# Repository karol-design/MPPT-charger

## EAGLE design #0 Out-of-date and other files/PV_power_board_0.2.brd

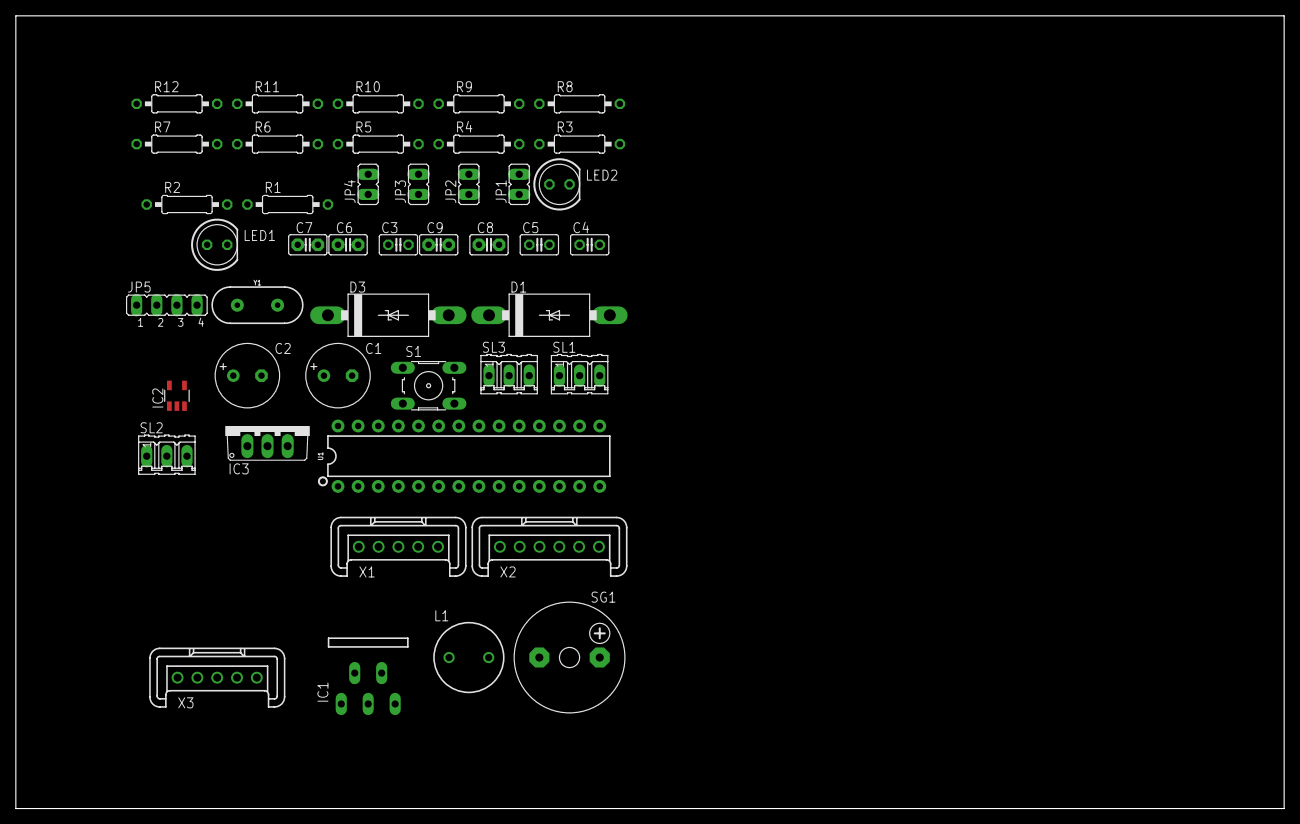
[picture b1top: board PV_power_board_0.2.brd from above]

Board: 2 copper layers, 160.0 x 100.0 mm, 44 parts (0 on the bottom side), 34 nets, no tracks yet.

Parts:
C1: 330µF; E3,5-8
C2: 100µF; E3,5-8
C3: 10µF; C025-025X050
C4: 0.33µF; C025-025X050
C5: 0.1µF; C025-025X050
C6, C7: 22p; C2.5-2
C8, C9: 100n; C2.5-2
D1: 1N5908; C4111-15
D3: STPS2L60; C4111-15
IC1: LM2576T; TO220-5
IC2: LMV358; SOT23-5
IC3: 7805TV; TO220V
JP1, JP2, JP3, JP4: JP1
JP5: JP4
L1: 330µH; 6000-XXXX-RC
LED1, LED2: LED5MM
R1, R12: 10k; 0207/10
R2: 33k; 0207/10
R3: 4.7k; 0207/10
R4, R6, R9: 1k; 0207/10
R5: 4.7; 0207/10
R7, R10: 120R; 0207/10
R8: 12k; 0207/10
R11: 220R; 0207/10
S1: B3F-10XX
SG1: F/CM12P
SL1: BATTERY; 03P
SL2: PV_PANEL; 03P
SL3: LOAD; 03P
U1: 328P; DIP28
X1: I_SENSOR; MKS1855-6-0-505
X2: BT_MODULE; MKS1856-6-0-606
X3: PROGRAM_PORT; MKS1855-6-0-505
Y1: 16MHz; HC49US

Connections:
+5V: C5.1, C9.2, IC2.5, IC3.3, JP4.2, JP5.4, LED1.A, R1.2, R12.1, U1.7, U1.20, X1.4, X3.5
BAT+: C1.+, C4.1, IC3.1, JP1.2, JP3.1, L1.1, R5.2, R8.1
BAT_VOLT: R5.1, R6.2, U1.25
DEV0: JP5.1, U1.27
DEV1: JP5.2, U1.26
FDBK: IC2.3, IC2.4, R9.1
GND: C1.-, C2.-, C3.2, C4.2, C5.2, C6.1, C7.1, C8.1, C9.1, D1.A, IC1.3, IC2.2, IC3.2, JP2.2, JP5.3, LED2.K, R4.1, R6.1, R7.2, S1.3, S1.4, SG1.-, SL1.2, SL1.3, SL3.2, SL3.3, U1.8, U1.22, X1.3, X2.4, X3.4
LM_ENABLE: IC1.5, R1.1
LM_FEEDBACK: IC1.4, R8.2, R9.2
LM_VIN: C2.+, IC1.1, R3.2, X1.2
unnamed: D1.C, IC1.2, L1.2
unnamed: C3.1, IC2.1, R2.1
unnamed: D3.C, X1.1
unnamed: LED1.K, R7.1
unnamed: D3.A, SL2.3
unnamed: JP1.1, SL3.1
unnamed: C6.2, U1.9, Y1.2
unnamed: R11.2, U1.14
unnamed: C7.2, U1.10, Y1.1
unnamed: JP3.2, SL1.1
unnamed: R10.2, U1.15
unnamed: LED2.A, R10.1
unnamed: C8.2, U1.21
unnamed: R11.1, SG1.+
unnamed: U1.6, X2.2
unnamed: U1.11, X2.3
unnamed: JP2.1, SL2.1, SL2.2
unnamed: JP4.1, X2.5
PV_CURRENT: U1.24, X1.5
PV_VOLT: R3.1, R4.2, U1.23
PWM: R2.2, U1.5
RESET: R12.2, S1.1, S1.2, U1.1, X3.1
RXD: U1.2, X3.3
TXD: U1.3, X3.2

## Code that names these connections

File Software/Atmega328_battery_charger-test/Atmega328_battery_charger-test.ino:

/*  Name: MPPT Solar Charger with Bluetooth communication | Battery charger test code
 *  Author: Karol Wojsław
 *  Date: 20/04/2021 (last release)
 *  Description: For test purposes only. This code is intended to be used for the test of 12V battery charger. For the test follow
 *  following procedure: Upload the code --> Connet the power supply --> Connect the battery --> Establish serial connection --> 
 *  --> Turn on the logger and validate first incoming data --> Leave the charger for >10 hours -->  Save and analyse the data
 *  
 *  Before the test change: timeMain, Vin_mV, Vout_float, Vout_bulk, V_ChargingDrop, PV_cur_Vofset
 */ 

#include <Wire.h>
#include <Adafruit_MCP4725.h>

/*Define pin allocations on Arduino board */
#define BAT_VOLT_PIN    A0
#define PV_VOLT_PIN     A1
#define PV_CURRENT_PIN  A2
#define LM_ENABLE_PIN   4

/*Fill in values below after callibration for improved precision of measurements and charger performance */
#define Vin_mV 5000 //Atmega328 supply voltage in mV - increased by - mV for more precise calculations (systematic error)
#define Vout_float 100 //Voltage that has to be set on FDBK pin to obtain float mode output voltage (13.70 V)
#define Vout_bulk 55 //Voltage that has to be set on FDBK pin to obtain float mode output voltage (14.65 V)
#define V_ChargingDrop 200 //Voltage to be subtracted when measureing the actual voltage on the battery
#define PV_cur_Vofset 320 //voltage in mV to be subtracted from PV_current sensor readings (systematic error)
#define R3  5150 
#define R4  980
#define R5  5070
#define R6  980

Adafruit_MCP4725 MCP4725_DAC; //Create MCP4725_DAC object

unsigned int n = 1; //Variable with current report issue

/*Define time intervals for different loops */
const unsigned long timeMain = 600000; //Time between main loop iterations (600000 ms = 600 seconds)


void setup(){
  //Input-output pin mode definition
  pinMode(BAT_VOLT_PIN, INPUT);
  pinMode(PV_VOLT_PIN, INPUT);
  pinMode(PV_CURRENT_PIN, INPUT);
  pinMode(LM_ENABLE_PIN, OUTPUT);

  //Output state change to default on startup
  digitalWrite(LM_ENABLE_PIN, HIGH); //Turn off LM2576 switching buck converter by default

  delay(10000); 

  Serial.begin(9600); //Standard serial port configuration (baud rate: 9600)
  Serial.print("Initialising charger code...\n");

  MCP4725_DAC.begin(0x60); //MCP4725 digital DAC I2C configuration (Adress: 0x60)
  SetCharging(Vout_float); //Set the charging voltage to Vout_float by default
  
  delay(5000);
}


void loop(){
  //Variables declaration
  unsigned long CHA_voltage, BAT_voltage, PV_voltage, PV_current, currentTime, tempTime, timeDifference = 0;
  bool Bulk = false;

  Serial.print("Main loop entered...\n\n"); //Header for logged data
  Serial.print("___________________________________________________________\n"); //Header for logged data
  Serial.print("No.\tMode\tCH_V\tBAT_V\tPV_V\tPV_I\tPower\tSOC\n"); //Header for logged data

  CHA_voltage = measureAverage(BAT_VOLT_PIN, 100, R5, R6); //Measure charging voltage
  /* Check state of charge of the battery before executing while loop and decide if Bulk or Float charging mode should be entered */
  digitalWrite(LM_ENABLE_PIN, HIGH); //Turn off LM2576 for measurements
  delay(1000); //Wait 1 second before the measurement
  BAT_voltage = measureAverage(BAT_VOLT_PIN, 100, R5, R6); //Measure battery voltage
  if(BAT_voltage < 13200){
    Bulk = true; //Set Bulk to 1 if the Battery voltage is lower than 13.2V
  }else{
    Bulk = false; //Set Bulk to 0 if the Battery voltage is higher than 13.2V
  }

  PV_voltage = measureAverage(PV_VOLT_PIN, 100, R3, R4);
  PV_current = (((measureAverage(PV_CURRENT_PIN, 100, 0, 1)-PV_cur_Vofset)*4)/6);
  generateReport(CHA_voltage, BAT_voltage, PV_voltage, PV_current, Bulk); //Send report over USB serial port

  /* Main loop of the code set to regularly check state of charge of the battery */
  while(true){
    currentTime = millis(); //Save current execution time
    tempTime = currentTime; //Set tempTime to currentTime at the beginning of the loop
    timeDifference = 0; //Set timeDifference to 0
    
    /* ------------------------------------------------------------ */
    /* ---------------- Enter bulk charging mode -------------------*/
    while(Bulk == true && timeDifference < timeMain){
      SetCharging(Vout_bulk); //Set the charging voltage to default Bulk voltage (14.65 V)
      digitalWrite(LM_ENABLE_PIN, LOW); //Turn on LM2576
      PV_current = (((measureAverage(PV_CURRENT_PIN, 100, 0, 1)*42)/60)-PV_cur_Vofset); //No voltage div, hence R1=0 & R2=1, 1 mA = 0.8 mV   
      if(PV_current < 300){
        Bulk = false;
      }
      
      delay(1000);

      currentTime = millis();
      timeDifference = currentTime - tempTime;  
    }

    /* ------------------------------------------------------------ */
    /* -------------- Enter float-storage charging mode ----------- */
    while(Bulk == false && timeDifference < timeMain){
      SetCharging(Vout_float); //Set the charging voltage to default float voltage (13.70 V)

      currentTime = millis();
      timeDifference = currentTime - tempTime; 
    }

    CHA_voltage = measureAverage(BAT_VOLT_PIN, 100, R5, R6); //Measure charging voltage
    PV_voltage = measureAverage(PV_VOLT_PIN, 100, R3, R4);
    PV_current = ((((measureAverage(PV_CURRENT_PIN, 100, 0, 1)-PV_cur_Vofset)*4)/6));
    
    /* Check state of charge of the battery and decide if Bulk or Float charging mode should be executed */
    digitalWrite(LM_ENABLE_PIN, HIGH); //Turn off LM2576 for measurements

    if(Bulk){
      delay(30000); //Wait 30 seconds before the measurement if the last mode was Bulk
    }else{
      delay(5000); //Wait 5 seconds before the measurement if the last mode was Float
    }
    
    BAT_voltage = measureAverage(BAT_VOLT_PIN, 100, R5, R6) - V_ChargingDrop; //Decrease measured V_ChargingDrop (Bat voltage higher immediatly after charging)
    if(BAT_voltage < 13100){
      Bulk = true; //Set Bulk to 1 if the Battery voltage is lower than 13.1V
    }else{
      Bulk = false; //Set Bulk to 0 if the Battery voltage is higher than 13.1V
    }

    generateReport(CHA_voltage, BAT_voltage, PV_voltage, PV_current, Bulk); //Send report over USB serial port
  }
}


/* -------------------------------------------------------------------------------------------------------------- */
/* Function that measure average of n readings from the input_pin and returns value in mV. Execution time:~5*n ms */
int measureAverage(int input_pin, int n, int V_div_R1, int V_div_R2){
  unsigned long readings_avr_mV, Vin_avr_mV, readings_sum = 0UL;
  for(int i = 0; i < n; i++){ //Take n measurements
    readings_sum += analogRead(input_pin); //Add a 10-bit (0-1024) value read to readings_sum
    delay(5); //Atmega328 takes ~0.1 ms to read an analog val. Wait 5 ms between readings for better performance 
  }
  readings_avr_mV = map((readings_sum / n), 0, 1024, 0, Vin_mV);
  Vin_avr_mV = (readings_avr_mV *((long)V_div_R1 + V_div_R2))/(V_div_R2);
  return Vin_avr_mV; //Return the average of n readings in mV
}


/* -------------------------------------------------------------------------------------------------------------- */
/* Function that change the charging voltage (LM2576 Vout) to a given value  */
void SetCharging(unsigned long Voltage_mV){
  MCP4725_DAC.setVoltage(Voltage_mV, false); //12-bit  resolution: values between 0 - 4095;  1.263mV per LSB (example for Vin 5.17 V)
  return;
}


/* -------------------------------------------------------------------------------------------------------------- */
/* Function that send a report on the current status of the charger through USB serial port */
void generateReport(int Cha_voltage, int BAT_voltage, int PV_voltage, int PV_current, bool Bulk){
  Serial.print(n);
  Serial.print("\t");
  Serial.print(Bulk);
  Serial.print("\t");
  Serial.print(Cha_voltage); //Charging voltage [mV]
  Serial.print("\t");
  Serial.print(BAT_voltage); //Battery panel current [mV]
  Serial.print("\t");
  Serial.print(PV_voltage); //PV panel voltage [mV]
  Serial.print("\t");
  Serial.print(PV_current); //PV panel current [mA]
  Serial.print("\t");
  Serial.print((PV_current * (long) PV_voltage) / 1000); //Power delivered [mW]
  Serial.print("\t");
  Serial.print((BAT_voltage - 11820)/13); //State of charge (SOC) [%]
  Serial.print("\n");

  n++; //Increment current report number
  return;
}

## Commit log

2021-04-02 Arduino file added to a folder
2021-04-02 Adding an introduction comment
2021-04-02 File organisation changes
2021-04-02 Update in the full software version
    - SetCharging function added
    - Bulk/Float charging
    - LM_ENABLE_PIN added
2021-04-03 Structure update
2021-04-03 Update in generate report function
2021-04-03 Mail loop, SetCharging, generateReport update
2021-04-03 Small changes in comments + LM2576 off for measurements
2021-04-03 Main loop update for report generation
2021-04-03 Buzzer, LED, PWM off by default
2021-04-03 Change in file organisation
2021-04-03 File organisation update
2021-04-03 File organisation change
2021-04-03 Exemplary PV cell I-V and P-V curves
2021-04-03 Var types update, MPPT algorithm implementation, initial charging voltage added,
2021-04-03 Variable updates
2021-04-03 Top comment update
2021-04-04 Arduino C++ Cheat Sheet added
2021-04-04 Update in file naming and organisation
2021-04-04 Measurement & Report Gen. Test Firmware
2021-04-04 MPPT algorithm test Firmware
2021-04-04 generateReport function update
2021-04-04 Changes in measureAverage function
2021-04-04 PV_current assignment changes
2021-04-04 Calibration values included
2021-04-04 Test code update (Measurements & Report)
2021-04-04 Notes update
2021-04-04 Conf. files changes
2021-04-05 Small changes in MPPT algorithm
2021-04-05 Notes update and research paper added
2021-04-05 Test photo documentation added
2021-04-05 Measurement delay time change
2021-04-07 Change in capacitor value
2021-04-07 Updates in Measurements & Report test software
2021-04-07 Updates: calibration, measurements, reports
2021-04-08 Additional jumper, notes file changes
2021-04-20 Update in the main Source Code
    Code not exactly consistent with the best current version - charger-test
2021-04-20 Changes in two test codes
2021-04-20 Battery charger test code added
2021-04-20 Update in Notes
2021-04-20 Small updates to notes
2021-04-20 Schematics update (MCP4725 connector, I2C)
2021-04-22 Update in tests folder organisation
2021-05-03 Hardware changes
2021-05-07 Hardware design files updated
2021-06-03 Minor changes in org files
2021-06-03 Test & callibration code created
2021-06-11 Callibration & tests code and reports
2021-06-16 Further changes in the test and calibration code
2021-06-16 Minor changes to manual battery charger files
2021-06-16 Voltage set proportional controller algorithm included
2021-06-16 Changes to setCharging method
2021-06-16 Updates to main program loop (menu)
2021-06-16 Debuging Serial.print lines added
2021-06-16 Changes to Manual battery charger test
2021-06-16 Minor changes to Serial prints
2021-06-16 Minor updates to manual_battery_charger code
2021-06-16 Photo documentation
2021-06-16 Test report data
2022-01-21 Files updated
2022-02-05 Restructure folders

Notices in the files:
parts and their libraries:
SparkFun-IC-Microcontroller: Licensing: Creative Commons ShareAlike 4.0 International - https://creativecommons.org/licenses/by-sa/4.0
